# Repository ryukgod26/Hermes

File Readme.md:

# Hermes
This is simple hermes board Created by me. It uses a Arduino Nano, 0.96 OLED Display, Ultra Sonic Sensor, DHT11 Temeperature/Humidity and a simple button. This shows the Temperature Data on the Screen First and when the Switch is pressed the data on the OLED Display get switchwd and started showing the data from the Ultra Sonic Sensor If there is a object in the range it shows how far is the object from the Ultra Sonic Sensor and if there is no object in he range then it shows "OUT OF RANGE!!".

## Zine

## Why
I built this Project to learn how to use Oled Display and connect different sensor with each other and know how to switch from reading data from one sensor to another. This was Learning Project built entirely to improve Hardware Skills.

## How to Use It

To use this project you just need to connect the sensors, switch and arduino nano with each other according to the wiring Diagram. Then clickConnect the Arduino nano with your computer with a USB Cable.  Then Open the arduino IDE and Select the COM port of the arduino Port. Then Upload the Code in Code/hermes_code Folder and upload that code to the arduino nano. Then It will Start Showing the Temperature of the Room to the Display and when you will press the switch then it will start reading the ultra sonic sensor and will tell the distance between the Object and the Ultra Sonic Sensor if there is a Object in range and Show that Distance in the Display.

## Required Hardware

- Arduino Nano X 1
- Ultra Sonic Sensor X 1
- Temperature and Humidity Sensor X 1
- 0.96 OLED Display X 1
- Simple Button X 1

## BOM (bill of Materials)

| Name | Quantity | Total Cost (USD) | Link | Distributor |
|------|----------|------------------|------|-------------|
| Arduino Nano | 1 | $2.00 | [Link](https://robu.in/product/arduino-nano-board-r3-with-ch340-chip-wo-usb-cable-solderedarduino-nano-r3-wo-usb-cable-soldered/) | Robu |
| OLED Display | 1 | $2.2 | [Link](https://robu.in/product/0-96-inch-ssd1306-white-oled-display-module/) | Robu |
| Push Buttons | 10 (only 1 is needed) | $0.2 | [Link](https://robu.in/product/6x6x5-tactile-push-button-switch/) | Robu |
| DHT11 Temperature Sensor| 1 | $0.5 | [Link](https://robu.in/product/dht11-digital-relative-humidity-temperature-sensor-module/) | Robu |
| Ultra Sonic Sensor | 1 | $1.23 | [Link](https://robu.in/product/3-3-5-5v-hc-sr04-ultrasonic-sensor-4pin/) | Robu |

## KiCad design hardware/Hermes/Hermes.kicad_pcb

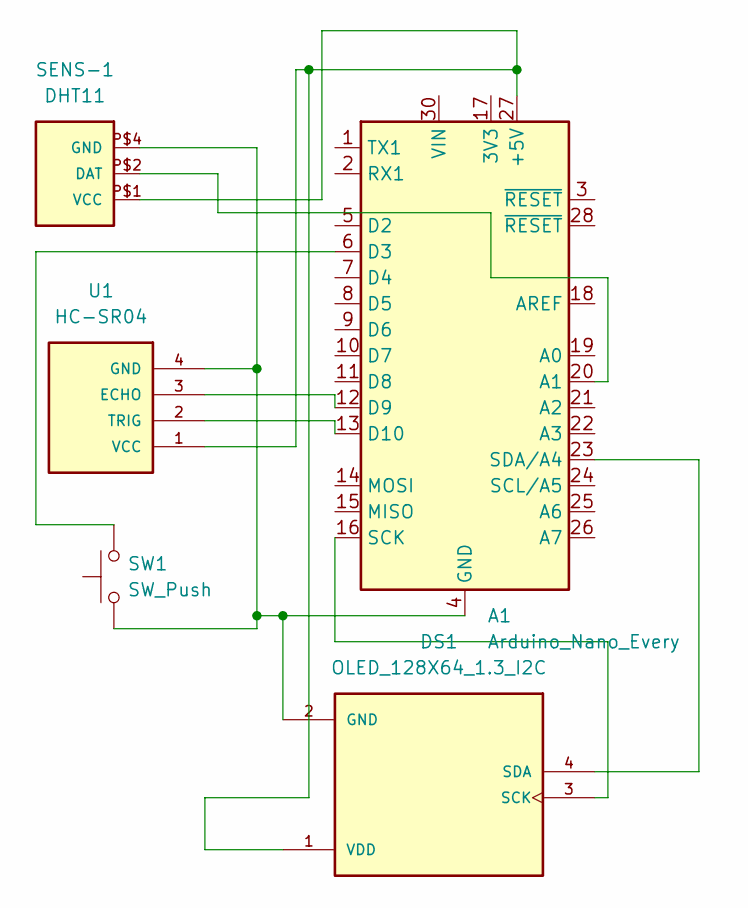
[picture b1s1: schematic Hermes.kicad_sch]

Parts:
A1: Arduino_Nano_Every; Arduino_Nano
DS1: OLED_128X64_1.3_I2C; LCD_OLED_128X64_1.3_I2C; PARTREV NA
SENS-1: DHT11; SENSOR-DHT11
SW1: SW_Push; SW_BUTT-2
U1: HC-SR04; XCVR_HC-SR04

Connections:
unnamed: A1.27 (+5V), DS1.1 (VDD), SENS-1.P$1 (VCC), U1.1 (VCC)
unnamed: A1.20 (A1), SENS-1.P$2 (DAT)
unnamed: A1.6 (D3), SW1.2
unnamed: A1.12 (D9), U1.3 (ECHO)
unnamed: A1.13 (D10), U1.2 (TRIG)
unnamed: A1.16 (SCK), DS1.3 (SCK)
unnamed: A1.23 (SDA/A4), DS1.4 (SDA)
unnamed: A1.4 (GND), A1.29 (GND), DS1.2 (GND), SENS-1.P$4 (GND), SW1.1, U1.4 (GND)

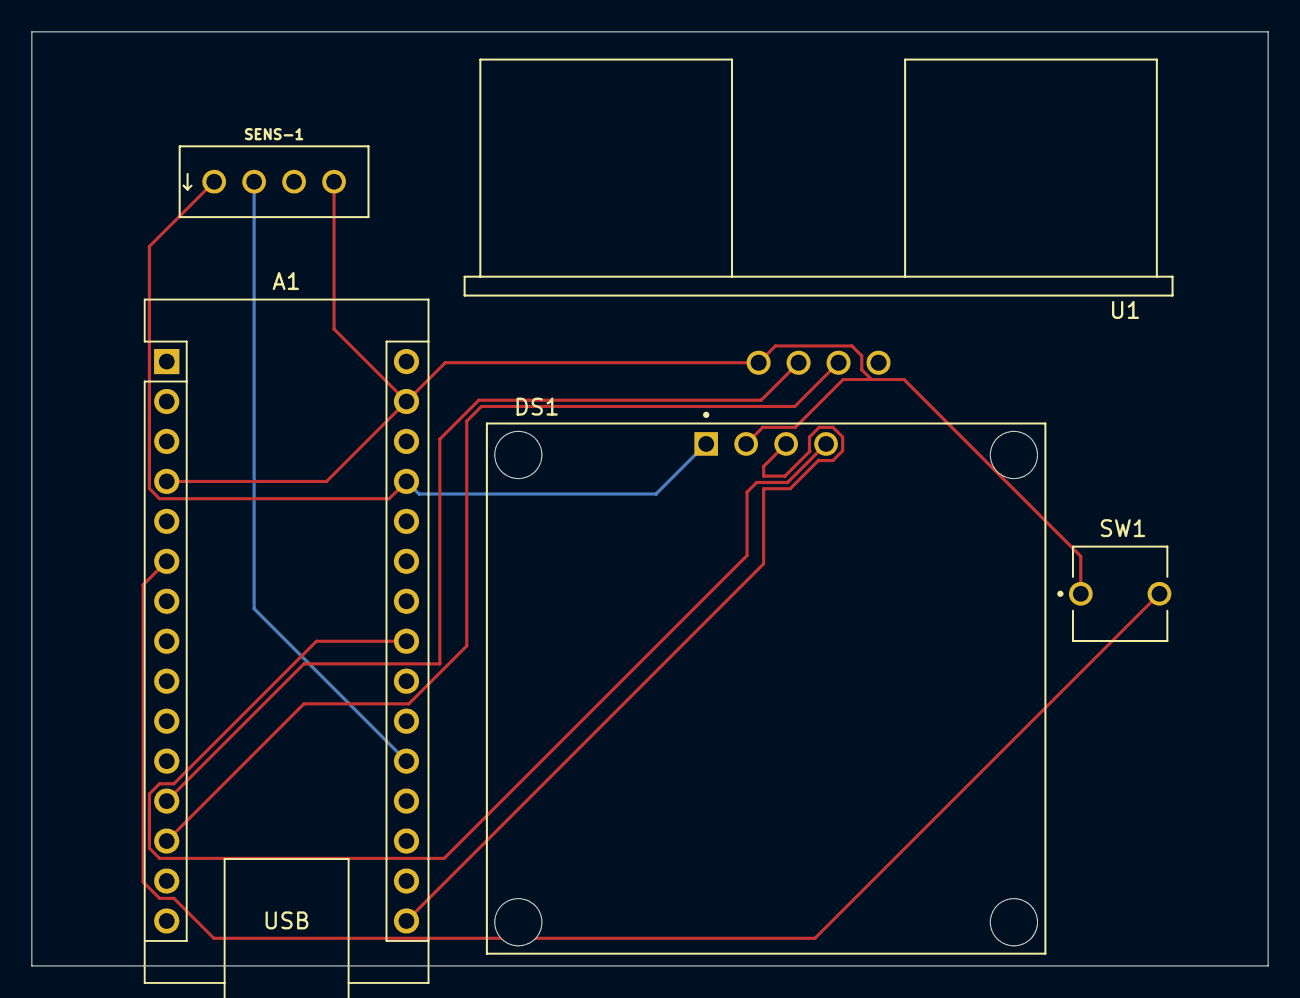
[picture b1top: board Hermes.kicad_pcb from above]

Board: 2 copper layers, 78.6 x 59.4 mm, 5 parts (0 on the bottom side), 8 nets.

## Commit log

2026-05-29 Added Pcb and schematics
2026-05-29 Added Arduino Code
2026-06-10 Add new components and update code for temperature and distance measurement
    - Updated fp-lib-table and sym-lib-table to include new libraries: LM393, DHT11, BUTT-2, HC-SR04, and ARDUINO_NANO.
    - Added LM393 component files including symbol and footprint.
    - Created a redirection HTML file for LM393 import instructions.
    - Modified the Arduino code to integrate DHT11 sensor for temperature and humidity readings.
    - Implemented button functionality to toggle between temperature and distance display modes.
    - Updated display logic to show sensor data based on the selected mode.
2026-06-10 Add new Gerber files for Hermes project and update job configuration
    - Created new Gerber files: Hermes-F_Mask.gbr, Hermes-F_Paste.gbr, Hermes-F_Silkscreen.gbr
    - Updated Hermes job configuration file (Hermes-job.gbrjob) with new file paths and specifications
    - Removed outdated backup zip file (Hermes-2026-06-10_174330.zip) and added a new backup (Hermes-2026-06-10_213705.zip)
    - Adjusted PCB settings in Hermes.kicad_pcb for output directory and drill shape
    - Updated project properties in Hermes.kicad_pro to reflect new plot directory
    - Made minor adjustments to schematic (Hermes.kicad_sch) for wire connections
2026-06-13 Added Readme
2026-06-16 Add XIAO family components and images to KiCad library
    - Created a new text file listing various XIAO family components including SAMD21, ESP32 variants, RP2040, and others.
    - Added multiple PNG images related to the XIAO family for visual reference in the library.
2026-06-16 Update Readme with wiring diagram and project purpose; adjust PCB design dimensions
2026-06-21 Add BOM, Zine files, and journal entries; update Readme with project details
2026-06-21 Fixed a small thing in readme
2026-06-21 Chnaged image size to A5
2026-06-21 Removed Comma from CSV
2026-06-21 Update Zine images: replace zine.jpg and zine.png with new versions
